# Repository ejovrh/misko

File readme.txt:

miško - the self sufficient gps tracker

1. ABOUT
	TODO
	Once upon a time, the need was to be able to geotag pictures I take with my camera while enjoying outdor activities.
	I order to satisfy this need I purchased the so-popular GPS recievers which run on a single AA battery (and have a bluetooth 
	transmitter) and a bluetooth module that attaches to the camera.
	This has proven to be futile because of battery runtime, storage capacity and so on.
	
	The original GPS tracker started its life as a (curiosity) kit from adafruit out of the need to have a 
		GPS tracker for my outdoor adventures which meets the following criteria:
			- does not run on AA batteries
			- has a sufficiently long standalone runtime
			- provides logging funcionality 
			- provides a bluetooth interface so that I can geotag pictures I take
			- can be charged by various means
			
		There are professional GPS devices which can (partly) do the job but they do cost a bit more than petty cash 
		and im not that rich.
		
		In my Searches on the Internet I did not find a product which has all the above features implemented; i did find, however, 
		a kit which provides logging of GPS data to a SD card.
		
		Now, GPS modules -usually- use the NMEA protocol; NMEA -usually- utilizes RS232 as a transport [TTL is another choice].
		RS232 is used by the kit's logic to parse incoming data and (RS232) can be easily fed into a bluetooth module.
		The camera has a bluetooth module - it is naturaly to experiment and see if this kit can be tailored to my needs.
		
		This repository attepts two things:
			- document the efforts of producing a suitable GPS tracker (its my university thesis, after all....)
			- produce a GPS tracker which has the following main features:
				- records GPS data and writes it to storage media (after vacations, google earth and the visited route are a nice thing to have)
				- provides NMEA sentences to the camera via bluetooth to geotag pictues
				- has sufficiently long runtime
				- comes in a waterproof box, is to some extent shockproof, dustproof and can handle some abuse
				- can be supplied with electricity on the road (by means of bicycle dynamo, solar cells, mains outlet)
				- can, if need be, charge my mobile phone
				- has certain functionalities user-configurable via buttons
				- displays certain tokens of inromation via LCD
				
				bonus features:
					- uploads the route at definable intervals to some server via GSM ( Big Mother is watching... )
					- log other interesting data to storage
					- get rid of the awful Arduino IDE and use a real one - AVR studio, for example
					
		That's the rough story of it...

2. SOFTWARE USED
	Arduino IED - an open source IDE for the atmel chips
		https://www.arduino.cc/en/Main/Donate
		note: in windows 7 you may need to manually opdate drivers 
		reason: it may be that the ATmega2560 board is not recognized with the stock OS driver
				the appropriate driver is located in the arduino installation
				go to device manager, find the faulty USB device, manually update driver from the arduino install path
		
	Arduino core libraries
		https://www.arduino.cc/en/Reference/Libraries
		SoftwareSerial, SD, EEPROM for interfacing various devices offered by the atmega2560

	Fritzing - an open source entry-level PCB design tool
		http://fritzing.org/download/?donation=0
		
	MS Visio 
		used for some diagrams

	AutoCAD 
		used for enclosure diagrams, stl files for 3D printing
		
	tortoise git
		https://tortoisegit.org/
		a frontend for GIT, utilizing the github repository
		"git for windows" is needed as the backend for communication/functionality of hte github repository
		
	git for windows
		https://git-for-windows.github.io/
		the backed for git-for-windows
			
	u8glib
		https://github.com/olikraus/u8glib
		a display driver library for all kinds of displays
		
	m2tklib
		https://github.com/olikraus/m2tklib
		an graphics library for all kinds of display devices

3. FILES / FOLDERS
	datasheets: contains datasheets, user guides for components
	misko-prototype: prototype firmware code which provides GPS tracker functionality
	battery holder.dwg: AutoCAD drawing of the battery holder
	LiIon battery.dwg: crude AutoCAD model of one battery, contains lateral dimensions
	prototype gps tracker - high level diagram.vsd: MSVisio diagram showing a high level overview of the hardware setup
	readme.txt: this file
	universal hardcase 50.dwg: crude AutoCAD drawing of the enclosure 
	
4. DEVICES
	4.1 misko-prototype
		The original hardware, in kit-form, lived its life in an Iphone3 box and has seen parts of the world on my bicycle.
		It worked well for its humble beginnings, but not well enough.
		Now it lives its life on a piece of cardboard, connected to breadboards, does not leave the home and serves as a 
		development instance.
		
		The role of this environment is development (hardware and software).
		
	4.2 misko-qa
		TODO
		The QA hardware/instance will be based on the prototype's schematics - PCB's tailored to fit into the enclosure and to 
		support features listed.
		Provided the PCB's are good (free of hardware bugs), it will serve as a software (and partially hardware) QA instance for the 
		jump of changes from development to production hardware.
	
	4.2 misko-prod
		TODO
		The production hardware/instance will be used in a live environment (real travels with rain and wind and everything).
		
		Changes on this environment will go through a controlled change cycle - first dev, then QA, then prod.
		
		Developers who know me from my work environment are entitled to my opinion and may now laugh as much as they want.
		
5. HARDWARE USED

	- Arduino Mega2560
		http://hr.rsdelivers.com/product/arduino/a000067/arduino-mega/7154084.aspx

	- Analog Devices TMP36FSZ Temperature Sensor 8-Pin SOIC
		http://hr.rsdelivers.com/product/analog-devices/tmp36fsz/analog-devices-tmp36fsz-temperature-sensor-8-pin-soic-40-125-c/0412973.aspx?query=TMP36FSZ
	
	- International Rectifier IRLZ44NSTRLPBF N-channel MOSFET Transistor, 47 A, 55 V, 3-Pin D2PAK
		http://hr.rsdelivers.com/product/international-rectifier/irlz44nstrlpbf/international-rectifier-irlz44nstrlpbf-n-channel-mosfet-transistor-47-a-55-v-3-pin-d2pak/8303417.aspx
		
	- Texas Instruments SN74AHC14D, Hex Schmitt Trigger Inverter, 8mA, 2 → 5.5 V, 14-Pin SOIC

		http://hr.rsdelivers.com/product/texas-instruments/sn74ahc14d/texas-instruments-sn74ahc14d-hex-schmitt-trigger-inverter-8ma-2-55-v-14-pin-soic/0526616.aspx
		
	- Atmel 2560
	
		http://hr.rsdelivers.com/catalogue/search.aspx?query=atmega2560&Family=9511#PI-1|viewtype-0|A-236854|
	
	- Microchip 23K256-I/SN SRAM Memory, 256kbit, 2.7 → 3.6 V, 25ns 8-Pin SOIC
	
		http://hr.rsdelivers.com/product/microchip/23k256-i-sn/microchip-23k256-i-sn-sram-memory-256kbit-27-36-v-25ns-8-pin-soic/6668148.aspx
		
	-

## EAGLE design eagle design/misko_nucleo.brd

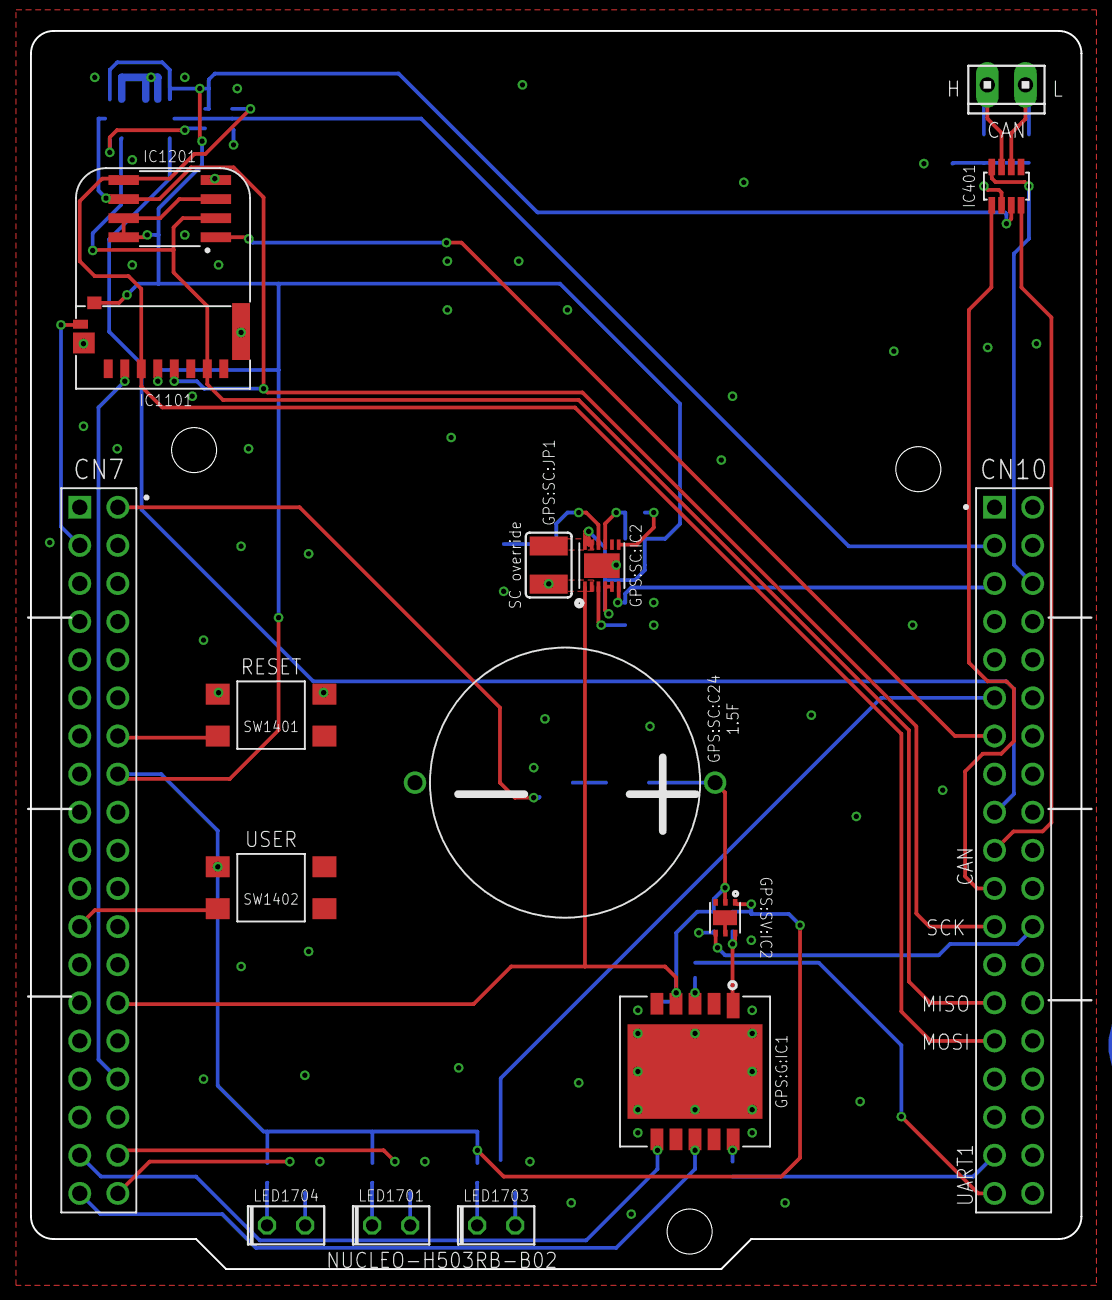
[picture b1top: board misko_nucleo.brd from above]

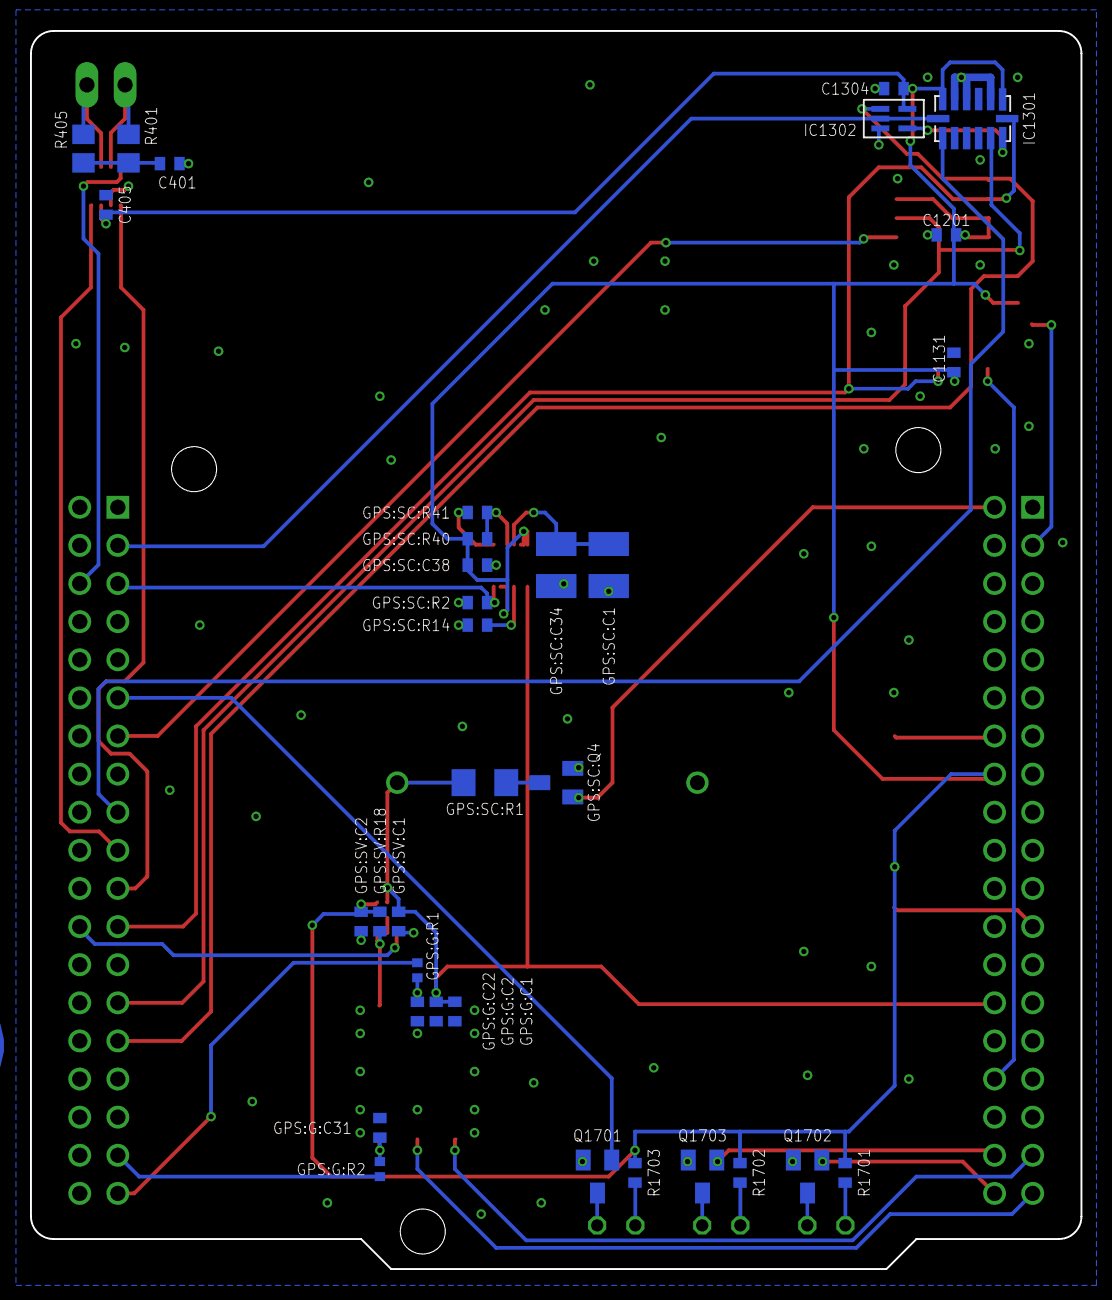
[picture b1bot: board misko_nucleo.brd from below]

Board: 2 copper layers, 70.0 x 82.5 mm, 48 parts (33 on the bottom side), 44 nets.

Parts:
BRD1: misko; NUCLEO-H503RB-B02
C401: 47nF / 10V; C0402
C405, C1131, C1201, C1304: 0.1u / 16V; C0402
GPS:G:C1: 0.1u / 16V; C0402
GPS:G:C2: 1u / 16V; C0402
GPS:G:C22, GPS:G:C31: 33p / 16V; C0402
GPS:G:IC1: ORG1510-MK4; SMD
GPS:G:R1, GPS:G:R2: 33R; R0402
GPS:SC:C1, GPS:SC:C34: 100u / 16V; C1210
GPS:SC:C24: 1.5F; TH
GPS:SC:C38: 0.1u / 16V; C0402
GPS:SC:IC2: LTC4425EDD#PBF; DFN-12
GPS:SC:JP1: SC override; SJW
GPS:SC:Q4: SQ2310ES-T1_BE3; SOT23
GPS:SC:R1: 33R; R1206
GPS:SC:R2, GPS:SC:R14: 10k; R0402
GPS:SC:R40, GPS:SC:R41: 150k; R0402
GPS:SV:C1, GPS:SV:C2: 0.1u / 16V; C0402
GPS:SV:IC2: TPS3808G33DBVT; WSON-6
GPS:SV:R18: 100k; R0402
IC401: TCAN334; SOT23-8
IC1101: 47309-2651; MICRO_SD_CONNECTOR
IC1201: FM25W256; SOIC08
IC1301: ADXL345; LGA14
IC1302: 74HCT1G32GW; SOT353/5
J1: CAN; 10X02MTA
LED1701: WP710A10SEC; LED2X5
LED1703: WP710A10LZGCK; LED2X5
LED1704: WP710A10SECK/J3; LED2X5
Q1701, Q1702, Q1703: SQ2310ES-T1_BE3; SOT23
R401, R405: 60; R0805
R1701: 55R; R0402
R1702: 65R; R0402
R1703: 33R; R0402
SW1401, SW1402: TL3305CF160QG; SMD

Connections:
3V3: BRD1.CN7_16, C405.1, C1131.1, C1201.1, C1304.1, GPS:SC:C38.1, GPS:SC:IC2.FB, GPS:SC:IC2.SEL, GPS:SC:IC2.VIN1, GPS:SC:IC2.VIN2, GPS:SC:JP1.2, GPS:SC:R40.2, GPS:SV:C2.1, GPS:SV:IC2.VDD, GPS:SV:R18.2, IC401.P$3, IC1101.DET, IC1101.VDD, IC1201.!HOLD!, IC1201.!WP!, IC1201.VCC, IC1301.VCC, IC1301.VDD, IC1302.VCC, R1701.2, R1702.2, R1703.2, SW1402.3, SW1402.4
ADC_VGPS: BRD1.CN7_28, GPS:G:C1.1, GPS:G:C2.1, GPS:G:IC1.4_VCC, GPS:SC:C24.+, GPS:SC:C34.1, GPS:SC:IC2.VOUT1, GPS:SC:IC2.VOUT2, GPS:SC:JP1.1, GPS:SC:R1.2, GPS:SV:C1.1, GPS:SV:IC2.SENSE
ADXL345:ADXL345SDA: IC1301.SDA, IC1302.Y
ADXL345_CS: BRD1.CN10_3, IC1301.!CS!, IC1302.A
ADXL345_INT1: BRD1.CN10_17, IC1301.INT1
CAN_!STBY!: BRD1.CN10_6, IC401.P$8
CAN_H: IC401.P$7, J1.1, R401.2
CAN_INFRA:SPLIT: C401.1, R401.1, R405.2
CAN_L: IC401.P$6, J1.2, R405.1
CAN_RX: BRD1.CN10_19, IC401.P$4
CAN_TX: BRD1.CN10_21, IC401.P$1
GND: BRD1.CN7_8, BRD1.CN7_19, BRD1.CN7_20, BRD1.CN7_22, BRD1.CN10_9, BRD1.CN10_20, BRD1.CN10_32, C401.2, C405.2, C1131.2, C1201.2, C1304.2, GPS:G:C1.2, GPS:G:C2.2, GPS:G:C22.2, GPS:G:C31.2, GPS:G:IC1.5_GND, GPS:G:IC1.GND1, GPS:G:IC1.GND2, GPS:G:IC1.GND4, GPS:G:IC1.GND5, GPS:G:IC1.GND6, GPS:G:IC1.GND7, GPS:G:IC1.GND8, GPS:G:IC1.GND9, GPS:G:IC1.GND10, GPS:G:IC1.GND12, GPS:G:IC1.GND13, GPS:G:IC1.GND14, GPS:G:IC1.GND15, GPS:SC:C1.2, GPS:SC:C24.-, GPS:SC:C38.2, GPS:SC:IC2.GND, GPS:SC:Q4.2, GPS:SC:R2.1, GPS:SC:R14.1, GPS:SV:C1.2, GPS:SV:C2.2, GPS:SV:IC2.GND1, GPS:SV:IC2.GND2, IC401.P$2, IC1101.GND1, IC1101.GND2, IC1101.GND3, IC1201.GND, IC1301.GND1, IC1301.GND2, IC1301.GND3, IC1302.GND, Q1701.2, Q1702.2, Q1703.2, SW1401.3, SW1401.4
GPS:G:GPS_RX: GPS:G:C31.1, GPS:G:IC1.RX_10, GPS:G:R2.2
GPS:G:GPS_TX: GPS:G:C22.1, GPS:G:IC1.3_TX, GPS:G:R1.2
GPS:GPS_ON_OFF: GPS:G:IC1.1_ON_OFF, GPS:SV:IC2.!RESET!, GPS:SV:R18.1
GPS:SC:PFI: GPS:SC:IC2.PFI, GPS:SC:R40.1, GPS:SC:R41.2
GPS:SC:PFI_RET: GPS:SC:IC2.PFI_RET, GPS:SC:R41.1
GPS:SC:PROG: GPS:SC:IC2.PROG, GPS:SC:R14.2
GPS:SC:SC_DIS_DRAIN: GPS:SC:Q4.3, GPS:SC:R1.1
GPS:SC:VMID: GPS:SC:C1.1, GPS:SC:C34.2, GPS:SC:IC2.VMID
GPS_!RESET!: BRD1.CN7_37, GPS:G:IC1.!RESET!_8
GPS_MCU_RX: BRD1.CN10_28, BRD1.CN10_35, GPS:G:R2.1
GPS_MCU_TX: BRD1.CN10_26, BRD1.CN10_37, GPS:G:R1.1
GPS_PWR_CTRL: BRD1.CN10_24, GPS:SV:IC2.!MR!
GPS_WKUP: BRD1.CN7_35, GPS:G:IC1.WAKEUP_6
LED:G_A: LED1703.A, Q1701.3
LED:G_C: LED1703.K, R1703.1
LED:R_A: LED1704.A, Q1702.3
LED:R_C: LED1704.K, R1701.1
LED:Y_A: LED1701.A, Q1703.3
LED:Y_C: LED1701.K, R1702.1
LED_GREEN: BRD1.CN10_11, Q1701.1
LED_RED: BRD1.CN7_38, Q1702.1
LED_YELLOW: BRD1.CN7_36, Q1703.1
NRST: BRD1.CN7_14, SW1401.1, SW1401.2
SD_CD: BRD1.CN7_3, IC1101.POL
SPI1_FRAM_CS: BRD1.CN10_13, IC1201.!CS!
SPI1_MISO: BRD1.CN10_27, IC1101.DAT0, IC1201.SO, IC1301.SDO
SPI1_MOSI: BRD1.CN10_29, IC1101.CMD, IC1201.SI, IC1302.B
SPI1_SCK: BRD1.CN10_23, IC1101.CLK, IC1201.SCK, IC1301.SCL
SPI1_SD_CS: BRD1.CN7_32, IC1101.CD/DAT3
SUPERCAP_!EN!: BRD1.CN10_5, GPS:SC:IC2.EN, GPS:SC:R2.2
SUPERCAP_DISCHARGE: BRD1.CN7_2, GPS:SC:Q4.1
USER_BUTTON: BRD1.CN7_23, SW1402.1, SW1402.2

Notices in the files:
parts and their libraries:
SparkFun-PowerIC: Licensing: CC v3.0 Share-Alike You are welcome to use this library for commercial purposes.
Wurth_Elektronik_Electromechanic_Switch_: Copyright: Würth Elektronik
